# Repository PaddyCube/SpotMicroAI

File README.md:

# SpotMicroAI 
 My Version of SpotMicroAI

# Low Level Firmware
 This package contains a low-level firmware for SpotMicroAI robot and might be useful for other 4-legged robots as well.
 The firmware runs on a Wemos D1 mini pro and should also run on any other ESP8266 device like NodeMCU.
 
 Calculating and processing the pose of all 12 servo joints is a complex task and a lot of work to implement in Arduino.
 But this can be done more easily and fast using ROS (Robot Operating System). So this firmware is designed to receive commands
 from ROS and just executes the synchronuous servo movement.
 
 To establish communication, rosserial is used as well as a rosserial implementation over wifi. The idea behind is, that you can either ROS on 
 RPI (or others) inside the robot and connect it to ESP8266 using serial connection. Or you can run ROS on any PC inside your local network and send
 commands to robot using wifi.

# Current state
## Settings
### Menu
The firmware provides some factory defaults for all settings. However, you can change all settings using serial console. If you start serial console, hit 'm' to enter main menu. The main menu provides some functionalities to show and change the settings. All settings can be stored to EEPROM of ESP8266.

<p>
-----------MAIN MENU----------<br>
f=delete all USER settings (reset all user settings in EEPROM)<br>
s=save USER settings (save user settings to EEPROM)<br>
x=print current settings<br>
1=communications menu (setup ROS & WIFI)<br>
2=Servo settings<br>
m=move servo manual<br>
0=exit<br>
</p>

Please note, if you first upload this firmware to your robot, your EEPROM might be filled with corrupt data. Please clear your EEPROM by deleting all user settings (f)
### Serial connection
 <p>If you want to use rosserial over USB instead if wifi, you must uncomment this line in SpotMicro.ino <br>
 
#define USE_WIFI
</p>
otherwise you will be unable to communicate to ROS master. when using serial communication, serial console with menu shown above will 
be not reachable most time. Only during a short period (5 seconds) at boot (setup routine), you will be able to launch menu.
### Servo
 The firmware offers some servo-related settings (min, max, initial pose, offset, home position and inversion) for each servo. All these settings can be changed by serial console
 
### Wifi
 Currently, the firmware connects to wifi but doesn't read any package here. All wifi-related settings can be configured by serial console 

## Servo movement
 The firmware is able to drive any of the 16 servos attached to a PCA9685 expansion board using ServoEasing library.
 You can send commands to any servo using serial commands. To do this, connect ESP8266 to your PC, open serial monitor 
 and follow the instructions you see there.
 
## ROS
currently, firmware only publish "hello world" to show if rosserial implementation works correctly. Later on, I'll describe used message types here
 
# Next steps
- create a ROS node and ROS message to subscribe to a ROS master

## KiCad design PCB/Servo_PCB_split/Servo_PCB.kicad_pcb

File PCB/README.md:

# SpotMicroAI
 My Version of SpotMicroAI
 
 Attention: all PCB files and schematics provided here are never tested and will have lots of bugs.
 Don't use them to produce any PCB. They came without any warranty and will not work at all.
 
 Why are the files here?
 I've tested some PCB designs and didn't want to throw everything to paperbin. 
 My initial idea was to have some protection and consumption monitor for each servo.
 
 As all PCBs are too large and too expensive to produce, I never produced a single one.

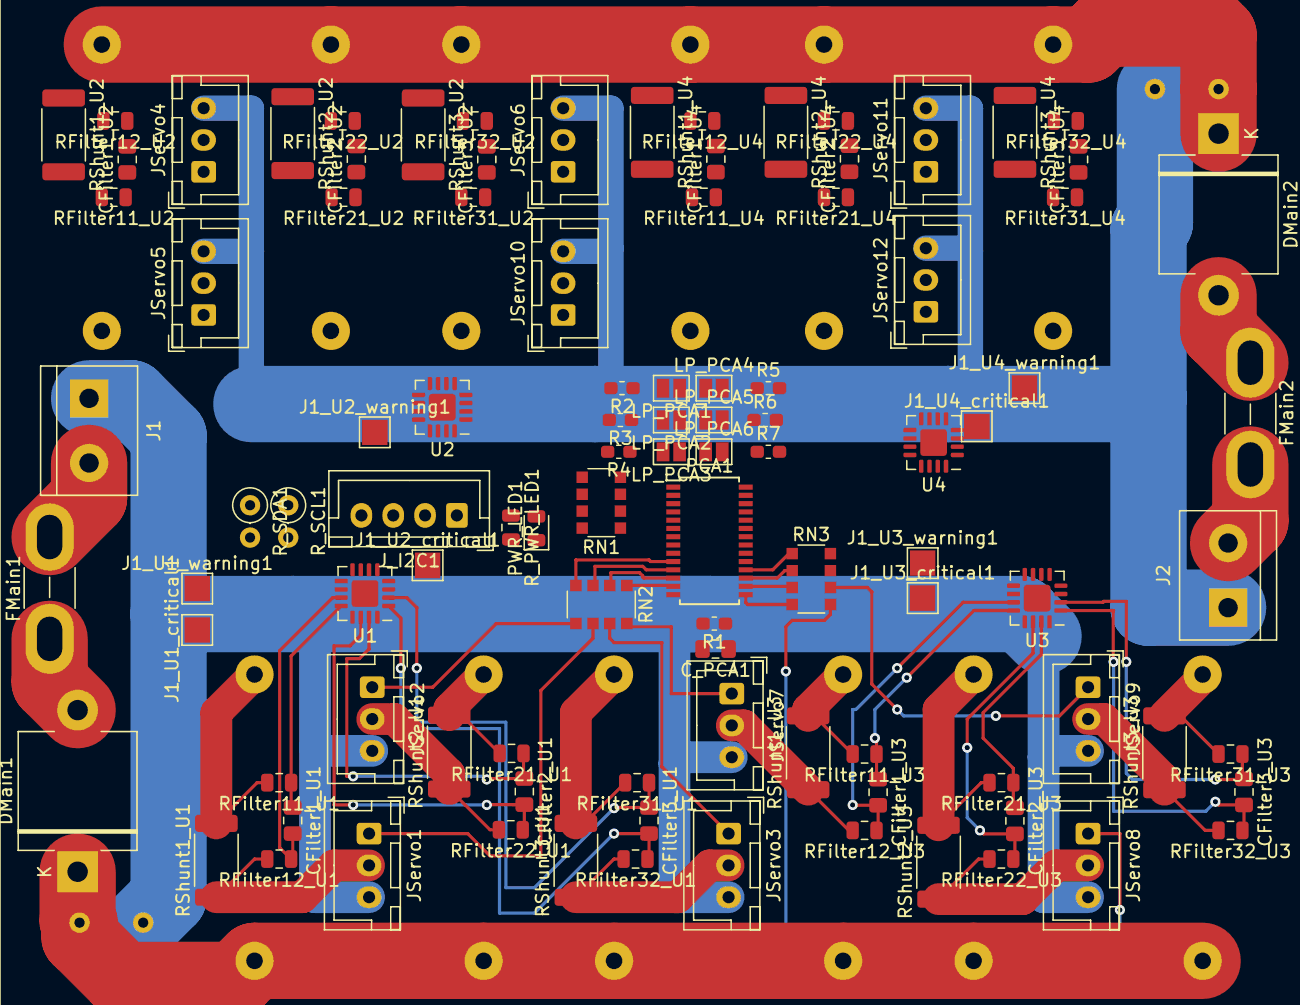
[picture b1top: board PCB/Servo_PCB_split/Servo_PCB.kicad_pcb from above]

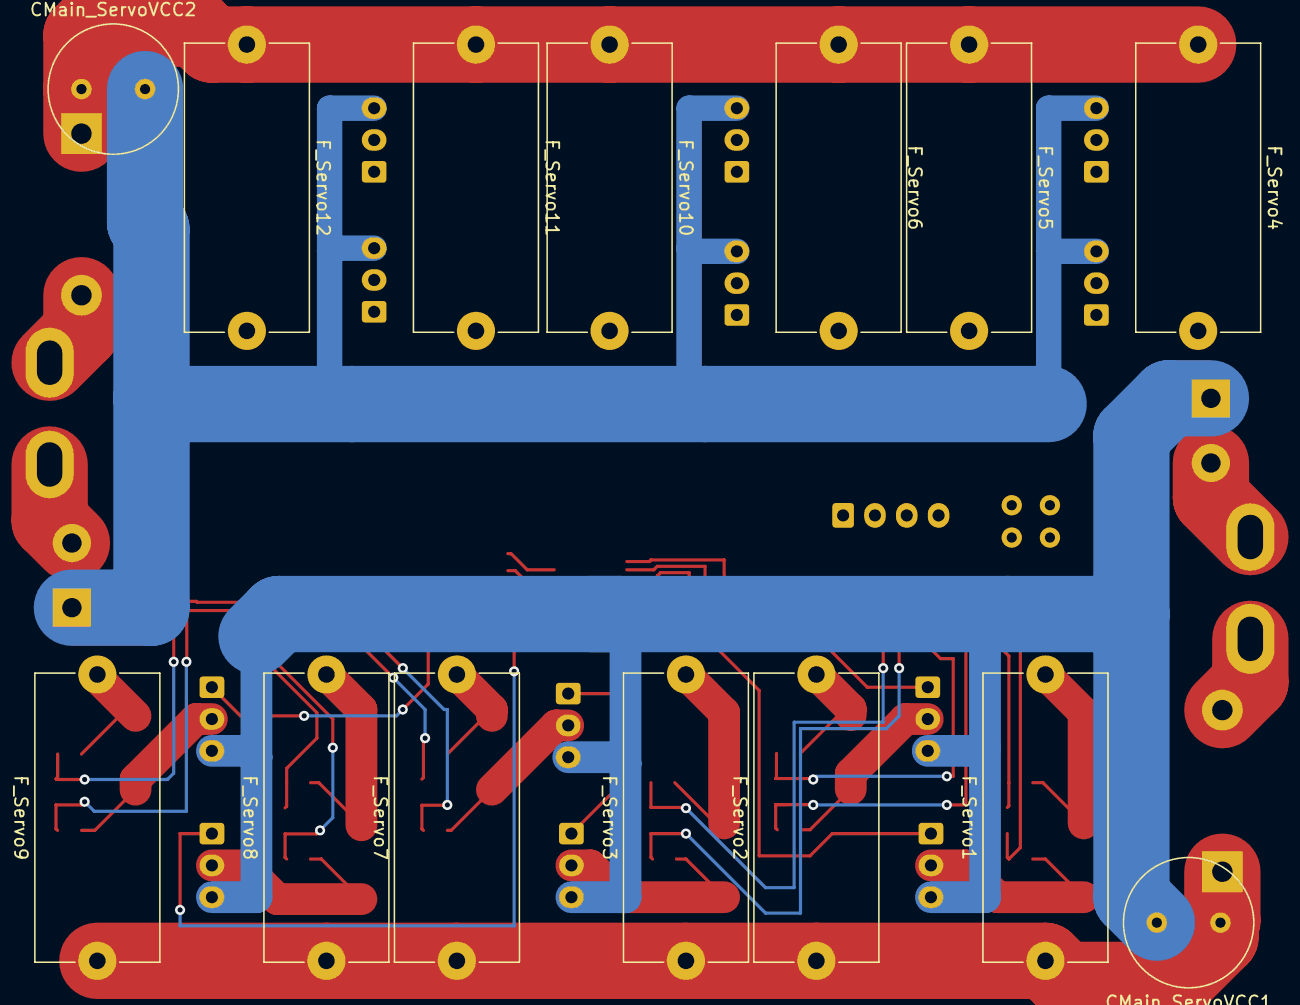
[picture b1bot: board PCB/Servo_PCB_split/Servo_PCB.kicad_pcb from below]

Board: 2 copper layers, 115 parts (14 on the bottom side), 101 nets.

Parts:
CFilter1_U1, CFilter1_U2, CFilter1_U3, CFilter1_U4, CFilter2_U1, CFilter2_U2, CFilter2_U3, CFilter2_U4, CFilter3_U1, CFilter3_U2, CFilter3_U3, CFilter3_U4: 1uF; C_0805_2012Metric_Pad1.15x1.40mm_HandSolder
CMain_ServoVCC1, CMain_ServoVCC2: 2200uF; C_Radial_D10.0mm_H16.0mm_P5.00mm
C_PCA1: 10uF; C_0805_2012Metric_Pad1.15x1.40mm_HandSolder
DMain1, DMain2: Schottky 30V25A; D_P600_R-6_P12.70mm_Horizontal
FMain1, FMain2: 20A; Fuse_Blade_Mini_directSolder
F_Servo1, F_Servo2, F_Servo3, F_Servo4, F_Servo5, F_Servo6, F_Servo7, F_Servo8, F_Servo9, F_Servo10, F_Servo11, F_Servo12: 5A; Fuseholder_Cylinder-5x20mm_Schurter_0031_8201_Horizontal_Op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
J1, J2: Screw_Terminal_01x02; TerminalBlock_bornier-2_P5.08mm
J1_U1_critical1, J1_U2_critical1, J1_U3_critical1, J1_U4_critical1: CRT; TestPoint_Pad_2.0x2.0mm
J1_U1_warning1, J1_U2_warning1, J1_U3_warning1, J1_U4_warning1: WRN; TestPoint_Pad_2.0x2.0mm
JServo1, JServo2, JServo3, JServo4, JServo5, JServo6, JServo7, JServo8, JServo9, JServo10, JServo11, JServo12: Conn_01x03; JST_XH_B3B-XH-A_1x03_P2.50mm_Vertical
J_I2C1: Conn_01x04; JST_XH_B4B-XH-A_1x04_P2.50mm_Vertical
LP_PCA1: A0; SolderJumper-2_P1.3mm_Open_Pad1.0x1.5mm
LP_PCA2: A1; SolderJumper-2_P1.3mm_Open_Pad1.0x1.5mm
LP_PCA3: A2; SolderJumper-2_P1.3mm_Open_Pad1.0x1.5mm
LP_PCA4: A3; SolderJumper-2_P1.3mm_Open_Pad1.0x1.5mm
LP_PCA5: A4; SolderJumper-2_P1.3mm_Open_Pad1.0x1.5mm
LP_PCA6: A5; SolderJumper-2_P1.3mm_Open_Pad1.0x1.5mm
PCA1: PCA9685PW; TSSOP-28_4.4x9.7mm_P0.65mm
PWR_LED1: Green; LED_0805_2012Metric
R1, R2, R3, R4, R5, R6, R7: 10K; R_0603_1608Metric_Pad1.05x0.95mm_HandSolder
RFilter11_U1, RFilter11_U2, RFilter11_U3, RFilter11_U4, RFilter12_U1, RFilter12_U2, RFilter12_U3, RFilter12_U4, RFilter21_U1, RFilter21_U2, RFilter21_U3, RFilter21_U4, RFilter22_U1, RFilter22_U2, RFilter22_U3, RFilter22_U4, RFilter31_U1, RFilter31_U2, RFilter31_U3, RFilter31_U4, RFilter32_U1, RFilter32_U2, RFilter32_U3, RFilter32_U4: 10; R_0805_2012Metric
RN1: 200Ohm; R_Array_Convex_4x1206
RN2, RN3: 200; R_Array_Convex_4x1206
RShunt1_U1, RShunt1_U2, RShunt1_U3, RShunt1_U4, RShunt2_U1, RShunt2_U2, RShunt2_U3, RShunt2_U4, RShunt3_U1, RShunt3_U2, RShunt3_U3, RShunt3_U4: 0.05; R_2512_6332Metric
R_PWR_LED1: 470; R_0805_2012Metric
R_SCL1: 10K; R_Axial_DIN0207_L6.3mm_D2.5mm_P2.54mm_Vertical
R_SDA1: 10K; R_Axial_DIN0207_L6.3mm_D2.5mm_P2.54mm_Vertical
U1: INA3221 0x40; Texas_RGV_S-PVQFN-N16_EP2.1x2.1mm
U2: INA3221 0x41; Texas_RGV_S-PVQFN-N16_EP2.1x2.1mm
U3: INA3221 0x42; Texas_RGV_S-PVQFN-N16_EP2.1x2.1mm
U4: INA3221 0x43; Texas_RGV_S-PVQFN-N16_EP2.1x2.1mm

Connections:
GND: C_PCA1.2, J_I2C1.2, PCA1.14, PCA1.25, R1.2, R2.2, R3.2, R4.2, R5.2, R6.2, R7.2, R_PWR_LED1.2, U1.3, U1.5, U2.3, U3.3, U4.3
INA_VCC: C_PCA1.1, J_I2C1.1, LP_PCA1.1, LP_PCA2.1, LP_PCA3.1, LP_PCA4.1, LP_PCA5.1, LP_PCA6.1, PCA1.28, PWR_LED1.2, R_SCL1.1, R_SDA1.1, U1.4, U2.4, U2.5, U3.4, U4.4
unnamed: DMain1.2, FMain1.1
unnamed: DMain2.2, FMain2.1
unnamed: FMain1.2, J1.2
unnamed: FMain2.2, J2.2
unnamed: F_Servo1.2, RFilter11_U1.2, RShunt1_U1.2
unnamed: F_Servo2.2, RFilter21_U1.2, RShunt2_U1.2
unnamed: F_Servo3.2, RFilter31_U1.2, RShunt3_U1.2
unnamed: F_Servo4.2, RFilter11_U2.2, RShunt1_U2.2
unnamed: F_Servo5.2, RFilter21_U2.2, RShunt2_U2.2
unnamed: F_Servo6.2, RFilter31_U2.2, RShunt3_U2.2
unnamed: F_Servo7.2, RFilter11_U3.2, RShunt1_U3.2
unnamed: F_Servo8.2, RFilter21_U3.2, RShunt2_U3.2
unnamed: F_Servo9.2, RFilter31_U3.2, RShunt3_U3.2
unnamed: F_Servo10.2, RFilter11_U4.2, RShunt1_U4.2
unnamed: F_Servo11.2, RFilter21_U4.2, RShunt2_U4.2
unnamed: F_Servo12.2, RFilter31_U4.2, RShunt3_U4.2
unnamed: LP_PCA1.2, PCA1.1, R2.1
unnamed: LP_PCA2.2, PCA1.2, R3.1
unnamed: LP_PCA3.2, PCA1.3, R4.1
unnamed: LP_PCA4.2, PCA1.4, R5.1
unnamed: LP_PCA5.2, PCA1.5, R6.1
unnamed: LP_PCA6.2, PCA1.24, R7.1
unnamed: PCA1.6, RN1.4
unnamed: PCA1.7, RN1.3
unnamed: PCA1.8, RN1.2
unnamed: PCA1.9, RN1.1
unnamed: PCA1.10, RN2.4
unnamed: PCA1.11, RN2.3
unnamed: PCA1.12, RN2.2
unnamed: PCA1.13, RN2.1
unnamed: PCA1.15, RN3.4
unnamed: PCA1.16, RN3.3
unnamed: PCA1.17, RN3.2
unnamed: PCA1.18, RN3.1
unnamed: PCA1.23, R1.1
unnamed: PWR_LED1.1, R_PWR_LED1.1
PWM_Servo1: JServo1.1, RN2.6
PWM_Servo2: JServo2.1, RN2.5
PWM_Servo3: JServo3.1, RN2.7
PWM_Servo4: JServo4.1, RN1.6
PWM_Servo5: JServo5.1, RN1.8
PWM_Servo6: JServo6.1, RN1.7
PWM_Servo7: JServo7.1, RN2.8
PWM_Servo8: JServo8.1, RN3.5
PWM_Servo9: JServo9.1, RN3.6
PWM_Servo10: JServo10.1, RN3.7
PWM_Servo11: JServo11.1, RN3.8
PWM_Servo12: JServo12.1, RN1.5
SCA: U1.7, U2.7, U3.7, U4.7
SCL: J_I2C1.3, PCA1.26, R_SCL1.2, U4.5
SDA: J_I2C1.4, PCA1.27, R_SDA1.2, U1.6, U2.6, U3.5, U3.6, U4.6
Servo1_VCC: JServo1.2, RFilter12_U1.2, RShunt1_U1.1
Servo2_VCC: JServo2.2, RFilter22_U1.2, RShunt2_U1.1
Servo3_VCC: JServo3.2, RFilter32_U1.2, RShunt3_U1.1
Servo4_VCC: JServo4.2, RFilter12_U2.2, RShunt1_U2.1
Servo5_VCC: JServo5.2, RFilter22_U2.2, RShunt2_U2.1
Servo6_VCC: JServo6.2, RFilter32_U2.2, RShunt3_U2.1
Servo7_VCC: JServo7.2, RFilter12_U3.2, RShunt1_U3.1
Servo8_VCC: JServo8.2, RFilter22_U3.2, RShunt2_U3.1
Servo9_VCC: JServo9.2, RFilter32_U3.2, RShunt3_U3.1
Servo10_VCC: JServo10.2, RFilter12_U4.2, RShunt1_U4.1
Servo11_VCC: JServo11.2, RFilter22_U4.2, RShunt2_U4.1
Servo12_VCC: JServo12.2, RFilter32_U4.2, RShunt3_U4.1
Servo_GND1: CMain_ServoVCC1.2, J1.1, JServo1.3, JServo2.3, JServo3.3, JServo7.3, JServo8.3, JServo9.3
Servo_GND2: CMain_ServoVCC2.2, J2.1, JServo4.3, JServo5.3, JServo6.3, JServo10.3, JServo11.3, JServo12.3
Servo_VCC1: CMain_ServoVCC1.1, DMain1.1, F_Servo1.1, F_Servo2.1, F_Servo3.1, F_Servo7.1, F_Servo8.1, F_Servo9.1
Servo_VCC2: CMain_ServoVCC2.1, DMain2.1, F_Servo4.1, F_Servo5.1, F_Servo6.1, F_Servo10.1, F_Servo11.1, F_Servo12.1
U1_CRITICAL: J1_U1_critical1.1, U1.9
U1_IN+1: CFilter1_U1.1, RFilter11_U1.1, U1.12
U1_IN+2: CFilter2_U1.1, RFilter21_U1.1, U1.15
U1_IN+3: CFilter3_U1.1, RFilter31_U1.1, U1.2
U1_IN-1: CFilter1_U1.2, RFilter12_U1.1, U1.11
U1_IN-2: CFilter2_U1.2, RFilter22_U1.1, U1.14
U1_IN-3: CFilter3_U1.2, RFilter32_U1.1, U1.1
U1_WARNING: J1_U1_warning1.1, U1.8
U2_CRITICAL: J1_U2_critical1.1, U2.9
U2_IN+1: CFilter1_U2.1, RFilter11_U2.1, U2.12
U2_IN+2: CFilter2_U2.1, RFilter21_U2.1, U2.15
U2_IN+3: CFilter3_U2.1, RFilter31_U2.1, U2.2
U2_IN-1: CFilter1_U2.2, RFilter12_U2.1, U2.11
U2_IN-2: CFilter2_U2.2, RFilter22_U2.1, U2.14
U2_IN-3: CFilter3_U2.2, RFilter32_U2.1, U2.1
U2_WARNING: J1_U2_warning1.1, U2.8
U3_CRITICAL: J1_U3_critical1.1, U3.9
U3_IN+1: CFilter1_U3.1, RFilter11_U3.1, U3.12
U3_IN+2: CFilter2_U3.1, RFilter21_U3.1, U3.15
U3_IN+3: CFilter3_U3.1, RFilter31_U3.1, U3.2
U3_IN-1: CFilter1_U3.2, RFilter12_U3.1, U3.11
U3_IN-2: CFilter2_U3.2, RFilter22_U3.1, U3.14
U3_IN-3: CFilter3_U3.2, RFilter32_U3.1, U3.1
U3_WARNING: J1_U3_warning1.1, U3.8
U4_CRITICAL: J1_U4_critical1.1, U4.9
U4_IN+1: CFilter1_U4.1, RFilter11_U4.1, U4.12
U4_IN+2: CFilter2_U4.1, RFilter21_U4.1, U4.15
U4_IN+3: CFilter3_U4.1, RFilter31_U4.1, U4.2
U4_IN-1: CFilter1_U4.2, RFilter12_U4.1, U4.11
U4_IN-2: CFilter2_U4.2, RFilter22_U4.1, U4.14
U4_IN-3: CFilter3_U4.2, RFilter32_U4.1, U4.1
U4_WARNING: J1_U4_warning1.1, U4.8

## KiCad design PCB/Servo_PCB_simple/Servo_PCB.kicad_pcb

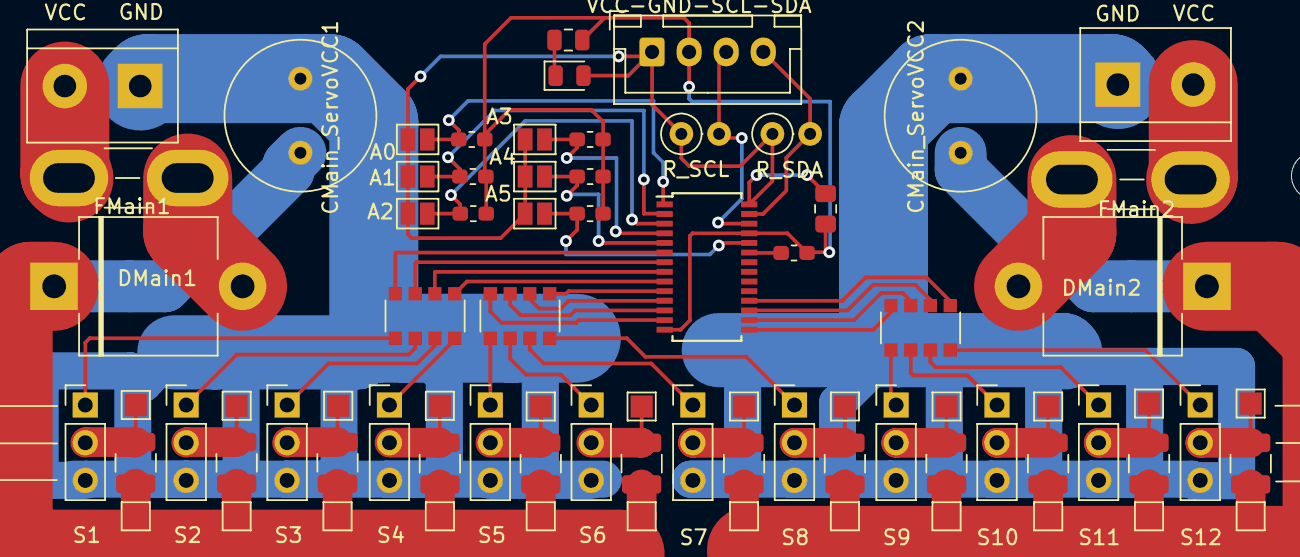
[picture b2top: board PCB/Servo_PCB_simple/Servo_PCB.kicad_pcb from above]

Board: 2 copper layers, 81 parts (0 on the bottom side), 56 nets.

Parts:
CMain_ServoVCC1, CMain_ServoVCC2: 2200uF; C_Radial_D10.0mm_H16.0mm_P5.00mm
C_PCA1: 10uF; C_0805_2012Metric_Pad1.15x1.40mm_HandSolder
DMain1, DMain2: Schottky 30V25A; D_P600_R-6_P12.70mm_Horizontal
FMain1, FMain2: 20A; Fuse_Blade_Mini_directSolder
H2, H3: MountingHole; MountingHole_3.2mm_M3
J1, J2: Screw_Terminal_01x02; TerminalBlock_bornier-2_P5.08mm
J_I2C1: Conn_01x04; JST_XH_B4B-XH-A_1x04_P2.50mm_Vertical
LP_PCA1: A0; SolderJumper-2_P1.3mm_Open_Pad1.0x1.5mm
LP_PCA2: A1; SolderJumper-2_P1.3mm_Open_Pad1.0x1.5mm
LP_PCA3: A2; SolderJumper-2_P1.3mm_Open_Pad1.0x1.5mm
LP_PCA4: A3; SolderJumper-2_P1.3mm_Open_Pad1.0x1.5mm
LP_PCA5: A4; SolderJumper-2_P1.3mm_Open_Pad1.0x1.5mm
LP_PCA6: A5; SolderJumper-2_P1.3mm_Open_Pad1.0x1.5mm
PCA1: PCA9685PW; TSSOP-28_4.4x9.7mm_P0.65mm
PWR_LED1: Green; LED_0805_2012Metric
R1, R2, R3, R4, R5, R6, R7: 10K; R_0603_1608Metric_Pad1.05x0.95mm_HandSolder
RN1: 200Ohm; R_Array_Convex_4x1206
RN2, RN3: 200; R_Array_Convex_4x1206
RShunt1, RShunt2, RShunt3, RShunt4, RShunt5, RShunt6, RShunt7, RShunt8, RShunt9: 0.05Ohm; R_1210_3225Metric
RShunt10, RShunt11, RShunt12: 0.05; R_1210_3225Metric
R_PWR_LED1: 470; R_0805_2012Metric
R_SCL: 10K; R_Axial_DIN0207_L6.3mm_D2.5mm_P2.54mm_Vertical
R_SDA: 10K; R_Axial_DIN0207_L6.3mm_D2.5mm_P2.54mm_Vertical
S1, S2, S3, S4, S5, S6, S7, S8, S9, S10, S11, S12: Conn_01x03; PinHeader_1x03_P2.54mm_Vertical
S1+1, S1-1, S2+1, S2-1, S3+1, S3-1, S4+1, S4-1, S5+1, S5-1, S6+1, S6-1: TestPoint; TestPoint_Pad_1.5x1.5mm
TP13, TP14, TP15, TP16, TP17, TP18, TP19, TP20, TP21, TP22, TP23, TP24: TestPoint; TestPoint_Pad_1.5x1.5mm

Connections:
GND: C_PCA1.2, J_I2C1.2, PCA1.14, PCA1.25, R1.2, R2.2, R3.2, R4.2, R5.2, R6.2, R7.2, R_PWR_LED1.2
INA_VCC: C_PCA1.1, J_I2C1.1, LP_PCA1.1, LP_PCA2.1, LP_PCA3.1, LP_PCA4.1, LP_PCA5.1, LP_PCA6.1, PCA1.28, PWR_LED1.2, R_SCL.1, R_SDA.1
unnamed: DMain1.2, FMain1.1
unnamed: DMain2.2, FMain2.1
unnamed: FMain1.2, J1.2
unnamed: FMain2.2, J2.2
unnamed: LP_PCA1.2, PCA1.1, R2.1
unnamed: LP_PCA2.2, PCA1.2, R3.1
unnamed: LP_PCA3.2, PCA1.3, R4.1
unnamed: LP_PCA4.2, PCA1.4, R5.1
unnamed: LP_PCA5.2, PCA1.5, R6.1
unnamed: LP_PCA6.2, PCA1.24, R7.1
unnamed: PCA1.6, RN2.4
unnamed: PCA1.7, RN2.3
unnamed: PCA1.8, RN2.2
unnamed: PCA1.9, RN2.1
unnamed: PCA1.10, RN1.1
unnamed: PCA1.11, RN1.2
unnamed: PCA1.12, RN1.3
unnamed: PCA1.13, RN1.4
unnamed: PCA1.15, RN3.4
unnamed: PCA1.16, RN3.3
unnamed: PCA1.17, RN3.2
unnamed: PCA1.18, RN3.1
unnamed: PCA1.23, R1.1
unnamed: PWR_LED1.1, R_PWR_LED1.1
PWM_Servo1: RN2.5, S1.1
PWM_Servo2: RN2.6, S2.1
PWM_Servo3: RN2.7, S3.1
PWM_Servo4: RN2.8, S4.1
PWM_Servo5: RN1.5, S5.1
PWM_Servo6: RN1.6, S6.1
PWM_Servo7: RN1.7, S7.1
PWM_Servo8: RN1.8, S8.1
PWM_Servo9: RN3.5, S9.1
PWM_Servo10: RN3.6, S10.1
PWM_Servo11: RN3.7, S11.1
PWM_Servo12: RN3.8, S12.1
SCL: J_I2C1.3, PCA1.26, R_SCL.2
SDA: J_I2C1.4, PCA1.27, R_SDA.2
Servo_GND1: CMain_ServoVCC1.2, J1.1, S1.3, S2.3, S3.3, S4.3, S5.3, S6.3
Servo_GND2: CMain_ServoVCC2.2, J2.1, S7.3, S8.3, S9.3, S10.3, S11.3, S12.3
Servo_VCC1: CMain_ServoVCC1.1, DMain1.1, RShunt1.1, RShunt2.1, RShunt3.1, RShunt4.1, RShunt5.1, RShunt6.1, S1+1.1, S2+1.1, S3+1.1, S4+1.1, S5+1.1, S6+1.1
Servo_VCC2: CMain_ServoVCC2.1, DMain2.1, RShunt7.1, RShunt8.1, RShunt9.1, RShunt10.1, RShunt11.1, RShunt12.1, TP13.1, TP15.1, TP17.1, TP19.1, TP21.1, TP23.1
Shunt_1_IN-: RShunt1.2, S1.2, S1-1.1
Shunt_2_IN-: RShunt2.2, S2.2, S2-1.1
Shunt_3_IN-: RShunt3.2, S3.2, S3-1.1
Shunt_4_IN-: RShunt4.2, S4.2, S4-1.1
Shunt_5_IN-: RShunt5.2, S5.2, S5-1.1
Shunt_6_IN-: RShunt6.2, S6.2, S6-1.1
Shunt_7_IN-: RShunt7.2, S7.2, TP14.1
Shunt_8_IN-: RShunt8.2, S8.2, TP16.1
Shunt_9_IN-: RShunt9.2, S9.2, TP18.1
Shunt_10_IN-: RShunt10.2, S10.2, TP20.1
Shunt_11_IN-: RShunt11.2, S11.2, TP22.1
Shunt_12_IN-: RShunt12.2, S12.2, TP24.1

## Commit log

2019-12-04 init load
2019-12-05 EEPROM function added
2019-12-05 test
2019-12-05 Fix for new version of ServoEasing library
2019-12-05 EEPROM implemented, more menus for settings
2019-12-05 code cleanup
2019-12-05 Update to readme
2020-01-13 Development Branch
2020-01-15 simple python gui to operate ROS node
2020-01-15 rosserial setup done, first hello world is working

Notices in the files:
PCB/Servo_PCB_simple/Servo_PCB.kicad_pcb:
(C) 2019 by Patrick Weber www.weberpatrick.de
